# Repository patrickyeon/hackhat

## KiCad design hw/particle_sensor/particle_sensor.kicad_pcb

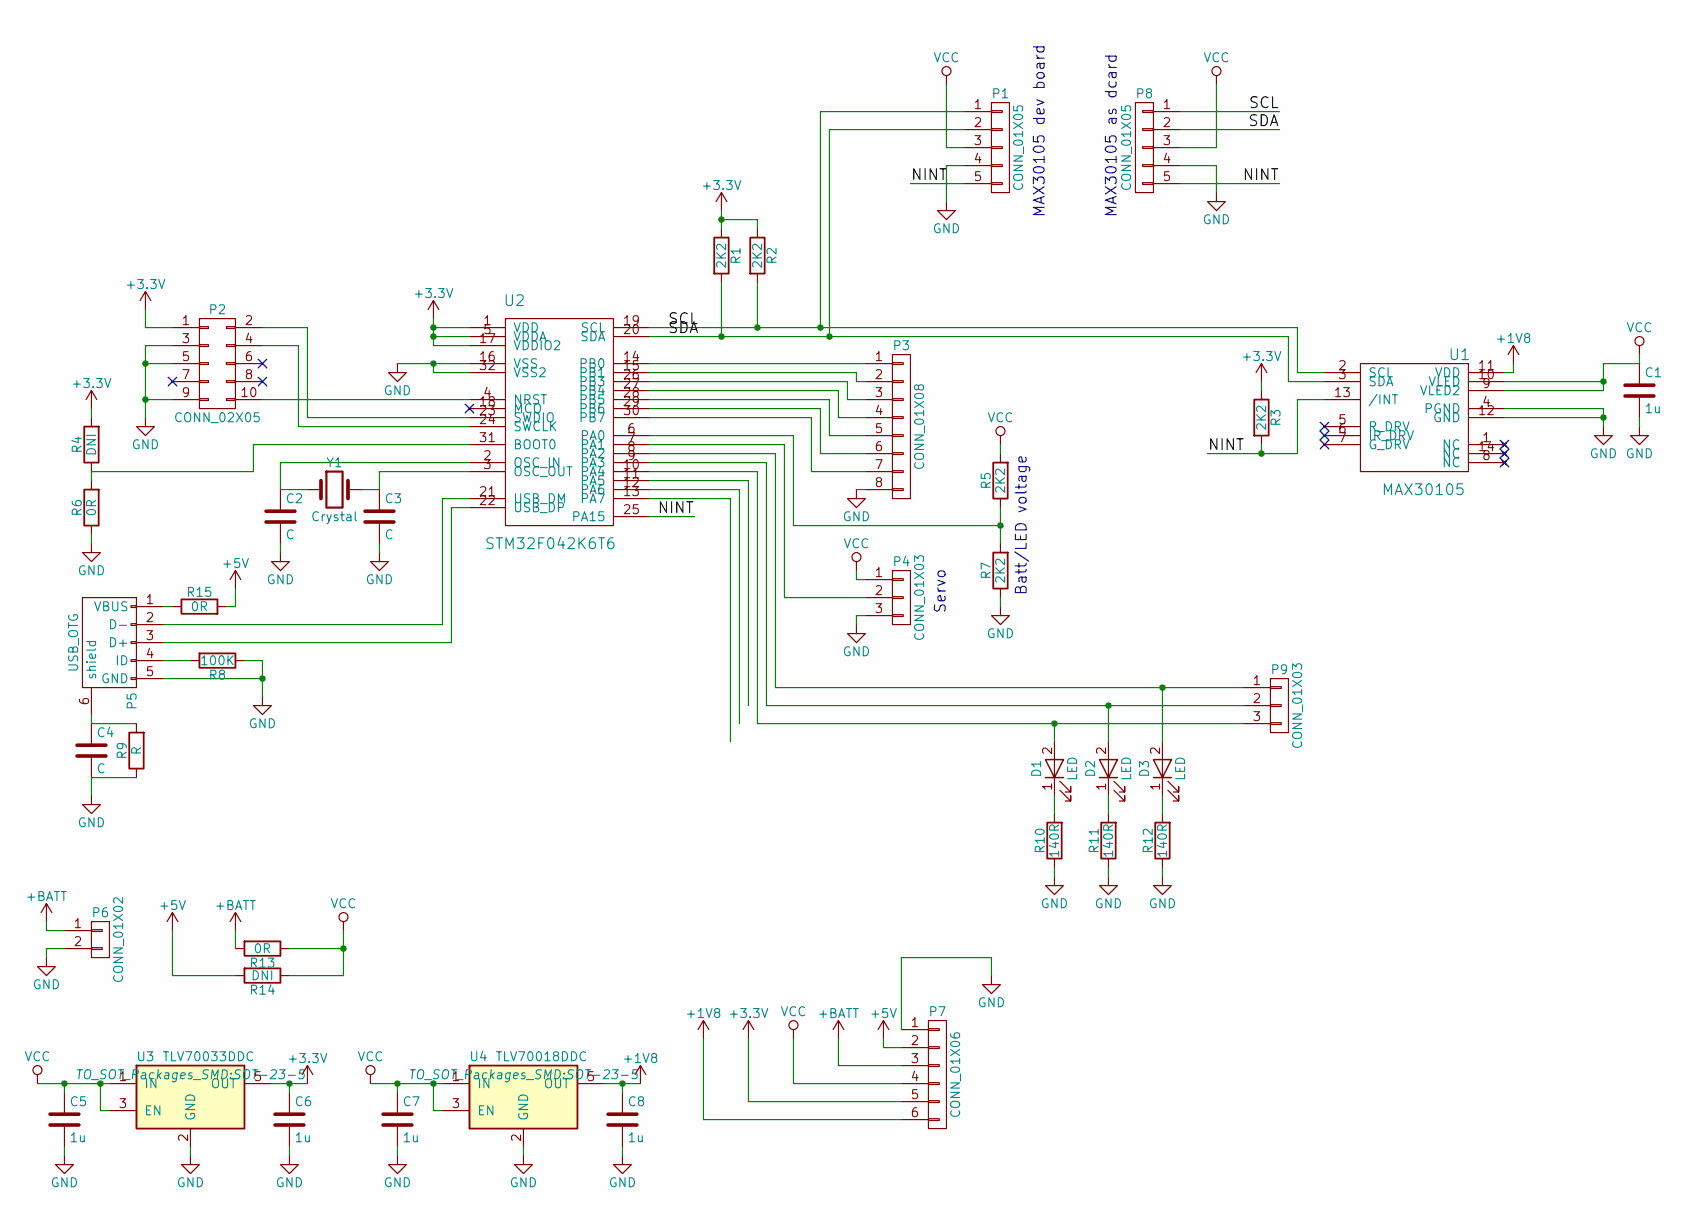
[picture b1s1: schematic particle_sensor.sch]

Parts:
C1, C5, C6, C7, C8: 1u; C_0603
C2, C3, C4: C; C_0603
D1, D2: LED; LED_2.1X1.6_RA
D3: LED; LED_2.1X1.6_RA; Digikey PN 1497-1175-1-ND
P1, P8: CONN_01X05; Socket_Strip_Straight_1x05
P2: CONN_02X05; CONN_JTAG_10; Digikey PN 1175-1629-ND
P3: CONN_01X08; Socket_Strip_Straight_1x08
P4, P9: CONN_01X03; Socket_Strip_Straight_1x03
P5: USB_OTG; USB_Micro-B
P6: CONN_01X02; Socket_Strip_Straight_1x02
P7: CONN_01X06; Socket_Strip_Straight_1x06
R1, R2, R3, R5, R7: 2K2; R_0603
R4, R14: DNI; R_0603
R6, R13, R15: 0R; R_0603
R8: 100K; R_0603
R9: R; R_0603
R10, R11, R12: 140R; R_0603
U1: MAX30105; 14_OESIP
U2: STM32F042K6T6; LQFP-32_7x7mm_Pitch0.8mm
U3: TLV70033DDC; SOT-23-5
U4: TLV70018DDC; SOT-23-5
Y1: Crystal; Crystal_HC49-SD_SMD

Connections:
+1V8: C8.1, P7.6, U1.11 (VDD), U4.5 (OUT)
+3V3: C6.1, P2.1, P7.5, R1.1, R2.1, R3.1, R4.2, U2.1 (VDD), U2.5 (VDDA), U2.17 (VDDIO2), U3.5 (OUT)
+5V: P7.2, R14.2, R15.2
+BATT: P6.1, P7.3, R13.2
/NINT: P1.5, P8.5, R3.2, U1.13 (/INT), U2.25 (PA15)
/SCL: P1.1, P8.1, R2.2, U1.2 (SCL), U2.19 (SCL)
/SDA: P1.2, P8.2, R1.2, U1.3 (SDA), U2.20 (SDA)
GND: C1.2, C2.2, C3.2, C4.2, C5.2, C6.2, C7.2, C8.2, P1.4, P2.3, P2.5, P2.9, P3.8, P4.3, P5.5 (GND), P6.2, P7.1, P8.4, R6.1, R7.1, R8.1, R9.1, R10.1, R11.1, R12.1, U1.4 (PGND), U1.12 (GND), U2.16 (VSS), U2.32 (VSS2), U3.2 (GND), U4.2 (GND)
unnamed: C2.1, U2.2 (OSC_IN), Y1.1
unnamed: C3.1, U2.3 (OSC_OUT), Y1.2
unnamed: C4.1, P5.6 (shield), R9.2
unnamed: D1.1 (K), R10.2
unnamed: D1.2 (A), P9.3, U2.10 (PA4)
unnamed: D2.1 (K), R11.2
unnamed: D2.2 (A), P9.2, U2.9 (PA3)
unnamed: D3.1 (K), R12.2
unnamed: D3.2 (A), P9.1, U2.8 (PA2)
unnamed: P2.2, U2.23 (SWDIO)
unnamed: P2.4, U2.24 (SWCLK)
unnamed: P2.10, U2.4 (NRST)
unnamed: P3.1, U2.14 (PB0)
unnamed: P3.2, U2.15 (PB1)
unnamed: P3.3, U2.26 (PB3)
unnamed: P3.4, U2.27 (PB4)
unnamed: P3.5, U2.28 (PB5)
unnamed: P3.6, U2.29 (PB6)
unnamed: P3.7, U2.30 (PB7)
unnamed: P4.2, U2.7 (PA1)
unnamed: P5.1 (VBUS), R15.1
unnamed: P5.2 (D-), U2.21 (USB_DM)
unnamed: P5.3 (D+), U2.22 (USB_DP)
unnamed: P5.4 (ID), R8.2
unnamed: R4.1, R6.2, U2.31 (BOOT0)
unnamed: R5.1, R7.2, U2.6 (PA0)
VCC: C1.1, C5.1, C7.1, P1.3, P4.1, P7.4, P8.3, R5.2, R13.1, R14.1, U1.9 (VLED2), U1.10 (VLED), U3.1 (IN), U3.3 (EN), U4.1 (IN), U4.3 (EN)

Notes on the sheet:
MAX30105 dev board
Servo
Batt/LED voltage
MAX30105 as dcard

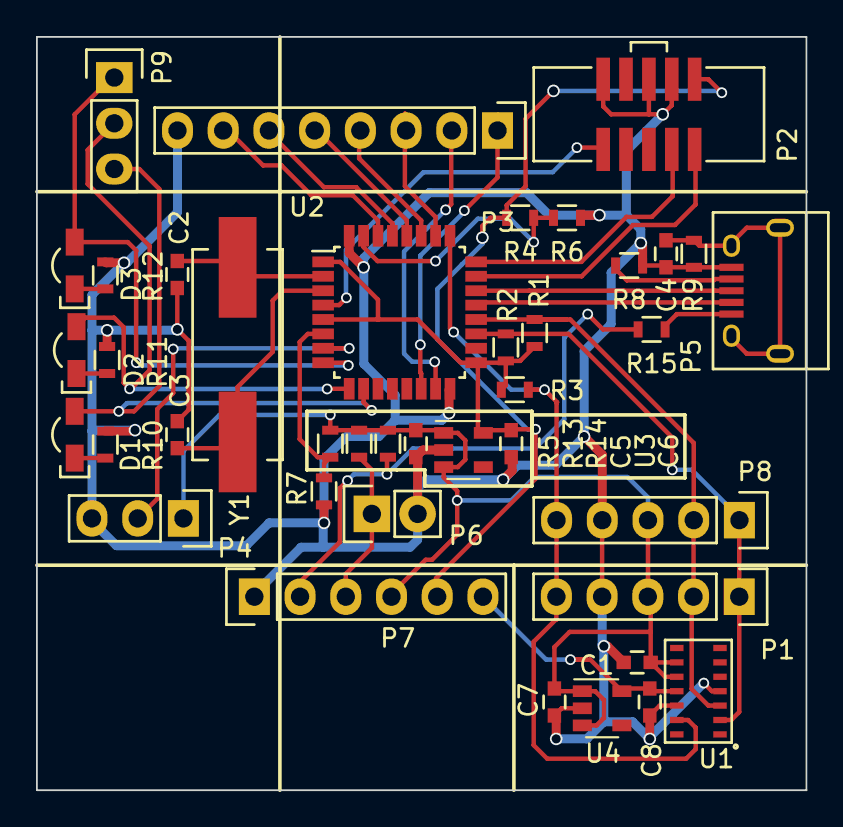
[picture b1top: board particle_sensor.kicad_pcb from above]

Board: 2 copper layers, 42.8 x 41.8 mm, 40 parts (0 on the bottom side), 35 nets.

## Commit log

2018-01-28 initial commit, LEDs and USB
2018-01-28 combo: untested ringbuffer and cleaner makefile
2018-01-28 Adding Unity unit testing framework
2018-01-29 ringbuffer and some testing to convince myself it works
2018-01-29 ringbuffer char -> uint8_t
2018-01-29 multi-ringbuffer fixed, and some simple USB control
2018-01-31 basics of 'immediate control' over USB
2018-08-27 basic timing and servo control
2018-08-27 more lightweight LED PWMing
2018-08-28 barebones i2c with particle sensor working (read temperature)
2018-08-29 very basics of blink mode work
2018-08-29 splitting project into separate mains
2018-08-29 reorg and rename things
2018-08-31 use a range of 0..1000 instead of 0..999
2018-08-31 re-org, importing hardware design
2018-09-01 oops, make targets actually depend on src
2018-09-03 routine to try to avoid overflowing the ALC
